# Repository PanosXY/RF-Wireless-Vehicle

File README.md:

RF-Wireless-Vehicle
===================

Wireless vehicle commanded through joystick, linked by RF signals

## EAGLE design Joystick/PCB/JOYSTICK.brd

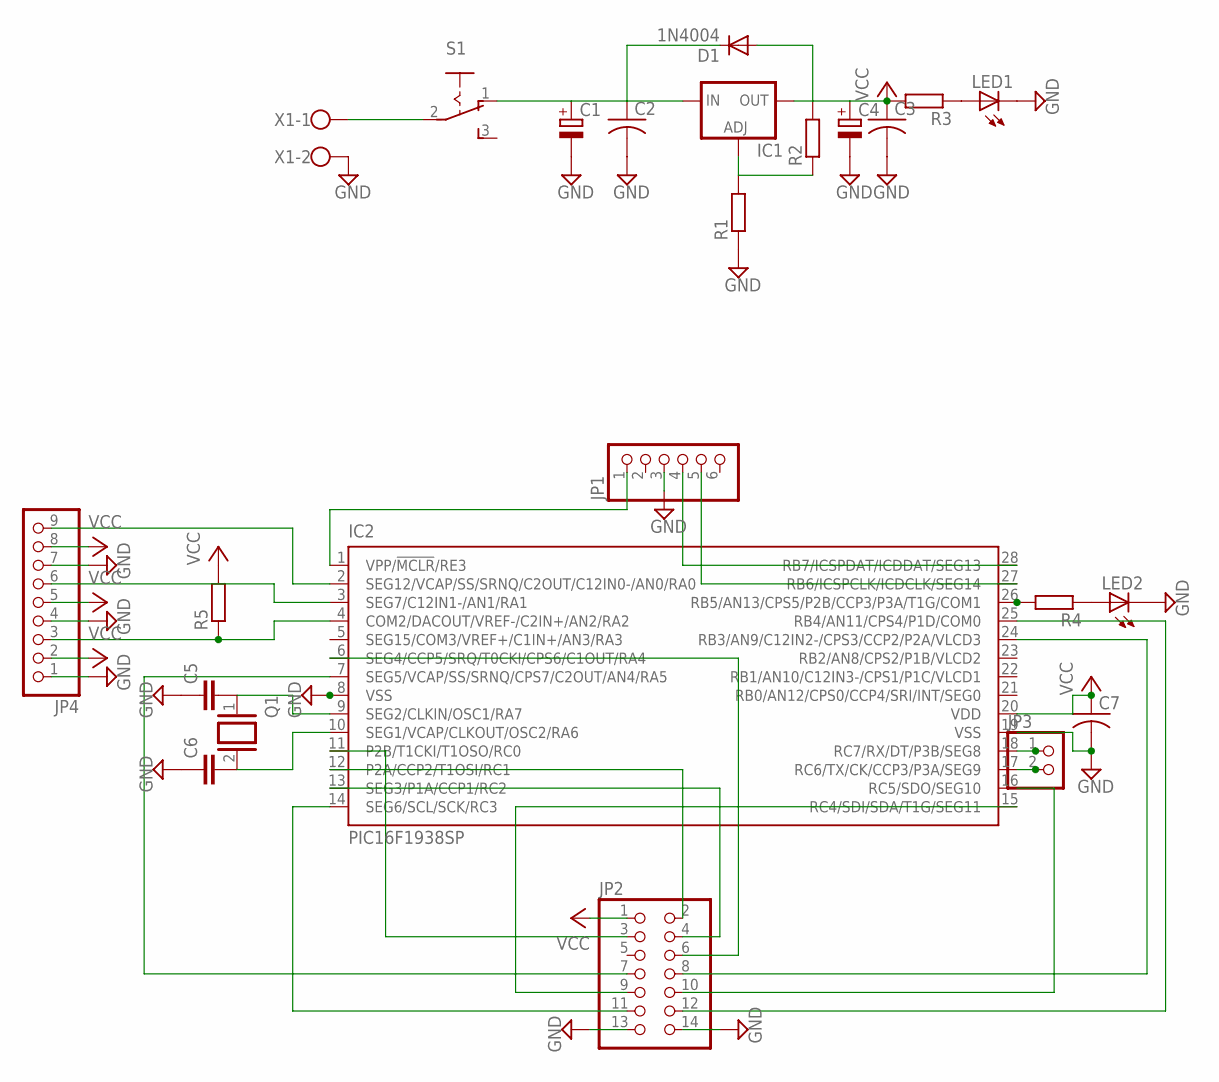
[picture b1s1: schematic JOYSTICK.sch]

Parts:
C1, C4: CPOL-EUE3.5-8; E3,5-8
C2, C3, C7: C-US050-030X075; C050-030X075
C5, C6: C-EU025-025X050; C025-025X050
D1: 1N4004; DO41-10
IC1: LM317TS; 317TS
IC2: PIC16F1938SP; DIL28-3
JP1: PINHD-1X6; 1X06
JP2: PINHD-2X7; 2X07
JP3: PINHD-1X2; 1X02
JP4: PINHD-1X9; 1X09
LED1, LED2: LED5MM
Q1: XTAL/S; QS
R1, R2, R3, R4, R5: R-EU_0207/10; 0207/10
S1: 255SB
X1: W237-102

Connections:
GND: C1.-, C2.2, C3.2, C4.-, C5.1, C6.1, C7.2, IC2.8 (VSS), IC2.19 (VSS), JP1.3, JP2.13, JP2.14, JP4.1, JP4.4, JP4.7, LED1.K (C), LED2.K (C), R1.1, X1.2
unnamed: S1.2, X1.1
unnamed: C1.+, C2.1, D1.C, IC1.3 (IN), S1.1 (O)
unnamed: IC2.11 (P2B/T1CKI/T1OSO/RC0), JP2.3
unnamed: LED1.A, R3.1
unnamed: IC1.1 (ADJ), R1.2, R2.1
unnamed: IC2.1 (VPP/!MCLR!/RE3), JP1.1
unnamed: IC2.2 (SEG12/VCAP/SS/SRNQ/C2OUT/C12IN0-/AN0/RA0), JP4.9
unnamed: IC2.3 (SEG7/C12IN1-/AN1/RA1), JP4.6
unnamed: IC2.4 (COM2/DACOUT/VREF-/C2IN+/AN2/RA2), JP4.3, R5.1
unnamed: IC2.12 (P2A/CCP2/T1OSI/RC1), JP2.2
unnamed: IC2.13 (SEG3/P1A/CCP1/RC2), JP2.4
unnamed: IC2.6 (SEG4/CCP5/SRQ/T0CKI/CPS6/C1OUT/RA4), JP2.6
unnamed: IC2.7 (SEG5/VCAP/SS/SRNQ/CPS7/C2OUT/AN4/RA5), JP2.7
unnamed: IC2.25 (RB4/AN11/CPS4/P1D/COM0), JP2.12
unnamed: IC2.24 (RB3/AN9/C12IN2-/CPS3/CCP2/P2A/VLCD3), JP2.8
unnamed: IC2.14 (SEG6/SCL/SCK/RC3), JP2.11
unnamed: IC2.15 (RC4/SDI/SDA/T1G/SEG11), JP2.9
unnamed: IC2.16 (RC5/SDO/SEG10), JP2.10
unnamed: IC2.17 (RC6/TX/CK/CCP3/P3A/SEG9), JP3.2
unnamed: IC2.18 (RC7/RX/DT/P3B/SEG8), JP3.1
unnamed: IC2.26 (RB5/AN13/CPS5/P2B/CCP3/P3A/T1G/COM1), R4.2
unnamed: IC2.27 (RB6/ICSPCLK/ICDCLK/SEG14), JP1.5
unnamed: IC2.28 (RB7/ICSPDAT/ICDDAT/SEG13), JP1.4
unnamed: C5.2, IC2.9 (SEG2/CLKIN/OSC1/RA7), Q1.1
unnamed: C6.2, IC2.10 (SEG1/VCAP/CLKOUT/OSC2/RA6), Q1.2
unnamed: LED2.A, R4.1
VCC: C3.1, C4.+, C7.1, D1.A, IC1.2 (OUT), IC2.20 (VDD), JP2.1, JP4.2, JP4.5, JP4.8, R2.2, R3.2, R5.2

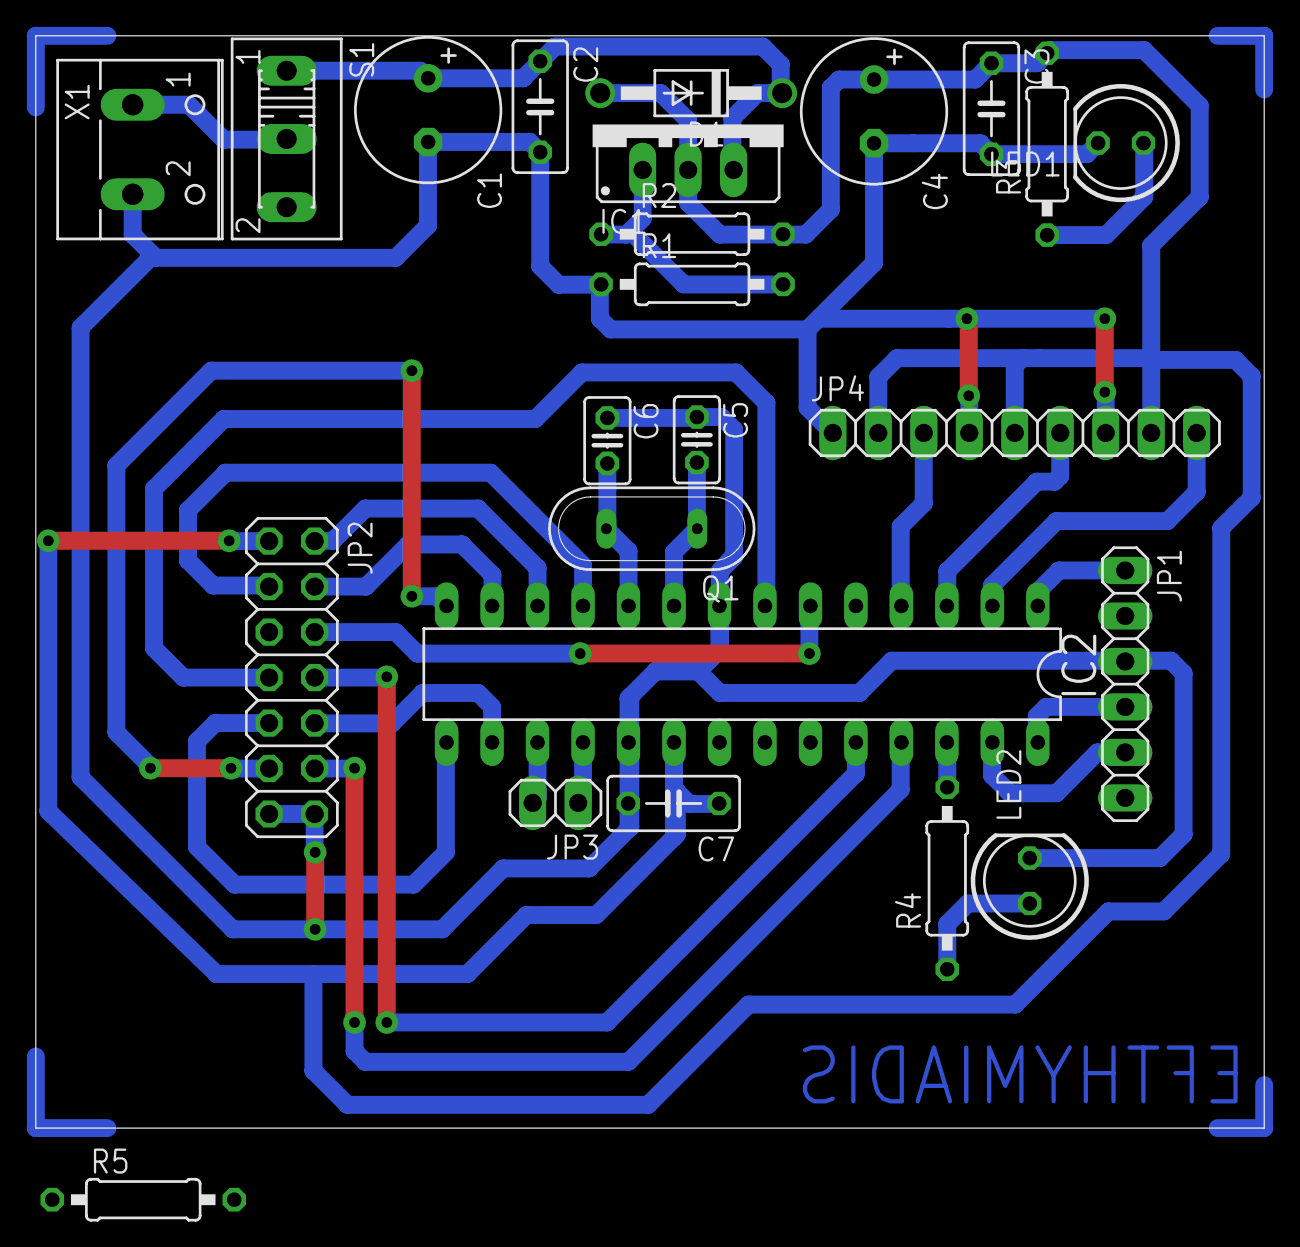
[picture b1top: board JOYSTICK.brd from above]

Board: 2 copper layers, 68.6 x 61.0 mm, 24 parts (0 on the bottom side), 28 nets.

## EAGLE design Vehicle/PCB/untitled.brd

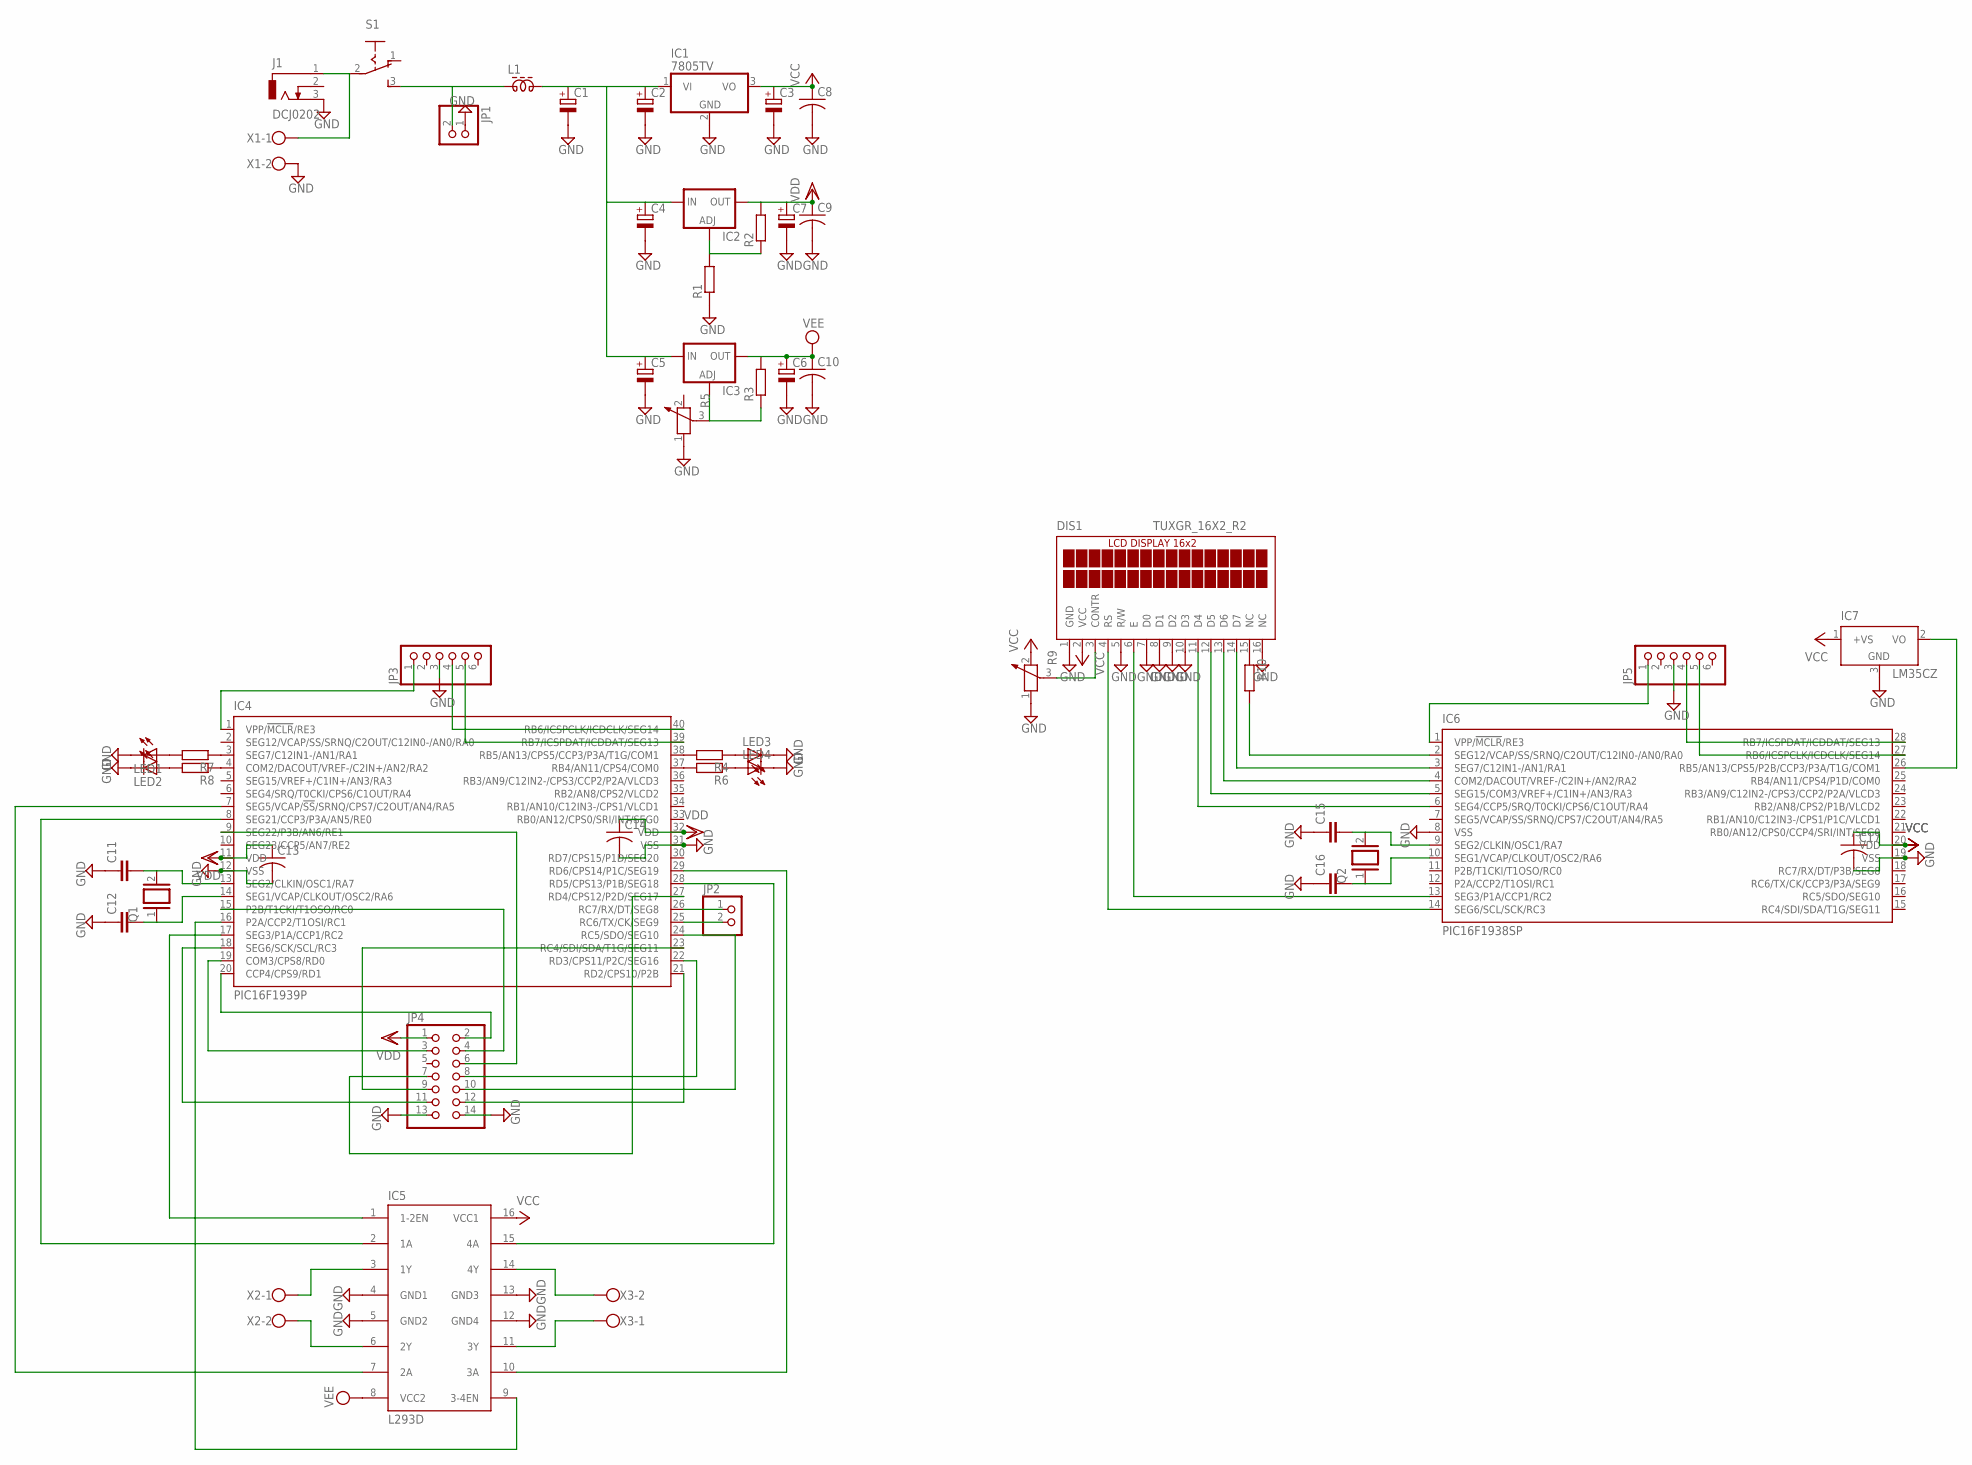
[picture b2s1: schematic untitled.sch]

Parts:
C1, C6: CPOL-EUE5-13; E5-13
C2, C3, C4, C5, C7: CPOL-EUE3.5-8; E3,5-8
C8, C9, C10, C13, C14, C17: C-US050-030X075; C050-030X075
C11, C12, C15, C16: C-EU025-025X050; C025-025X050
DIS1: TUXGR_16X2_R2
IC1: 7805TV; TO220V
IC2, IC3: LM317TS; 317TS
IC4: PIC16F1939P; DIL40
IC5: L293D; DIL16
IC6: PIC16F1938SP; DIL28-3
IC7: LM35CZ; TO92
J1: DCJ0202
JP1, JP2: PINHD-1X2; 1X02
JP3, JP5: PINHD-1X6; 1X06
JP4: PINHD-2X7; 2X07
L1: ZD60820512; ZD6-2W5
LED1, LED2, LED3, LED4: LED5MM
Q1, Q2: XTAL/S; QS
R1, R2, R3, R4, R6, R7, R8, R10: R-EU_0207/10; 0207/10
R5, R9: POTENTIOMETER_PT-10; PT-10
S1: 255SB
X1, X2, X3: W237-102

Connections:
GND: C1.-, C2.-, C3.-, C4.-, C5.-, C6.-, C7.-, C8.2, C9.2, C10.2, C11.1, C12.1, C13.2, C14.2, C15.1, C16.1, C17.2, DIS1.1 (GND), DIS1.5 (R/W), DIS1.7 (D0), DIS1.8 (D1), DIS1.9 (D2), DIS1.10 (D3), DIS1.16 (NC), IC1.2 (GND), IC4.12 (VSS), IC4.31 (VSS), IC5.4 (GND1), IC5.5 (GND2), IC5.12 (GND4), IC5.13 (GND3), IC6.8 (VSS), IC6.19 (VSS), IC7.3 (GND), J1.3, JP1.1, JP3.3, JP4.13, JP4.14, JP5.3, LED1.K (C), LED2.K (C), LED3.K (C), LED4.K (C), R1.1, R5.1, R9.1, X1.2
unnamed: JP1.2, L1.1, S1.3 (S)
unnamed: IC4.17 (SEG3/P1A/CCP1/RC2), IC5.1 (1-2EN)
unnamed: IC3.1 (ADJ), R3.1, R5.3
unnamed: J1.1, S1.2, X1.1
unnamed: C1.+, C2.+, C4.+, C5.+, IC1.1 (VI), IC2.3 (IN), IC3.3 (IN), L1.2
unnamed: IC4.26 (RC7/RX/DT/SEG8), JP2.1
unnamed: IC4.25 (RC6/TX/CK/SEG9), JP2.2
unnamed: IC2.1 (ADJ), R1.2, R2.1
unnamed: IC4.24 (RC5/SDO/SEG10), JP4.10
unnamed: IC4.1 (VPP/!MCLR!/RE3), JP3.1
unnamed: IC4.40 (RB6/ICSPCLK/ICDCLK/SEG14), JP3.4
unnamed: IC4.39 (RB7/ICSPDAT/ICDDAT/SEG13), JP3.5
unnamed: C12.2, IC4.14 (SEG1/VCAP/CLKOUT/OSC2/RA6), Q1.1
unnamed: C11.2, IC4.13 (SEG2/CLKIN/OSC1/RA7), Q1.2
unnamed: IC4.23 (RC4/SDI/SDA/T1G/SEG11), JP4.9
unnamed: IC4.18 (SEG6/SCK/SCL/RC3), JP4.11
unnamed: IC4.16 (P2A/CCP2/T1OSI/RC1), IC5.9 (3-4EN)
unnamed: IC4.20 (CCP4/CPS9/RD1), JP4.2
unnamed: IC4.19 (COM3/CPS8/RD0), JP4.3
unnamed: IC4.15 (P2B/T1CKI/T1OSO/RC0), JP4.4
unnamed: IC4.9 (SEG22/P3B/AN6/RE1), JP4.6
unnamed: IC4.27 (RD4/CPS12/P2D/SEG17), JP4.7
unnamed: IC4.21 (RD2/CPS10/P2B), JP4.12
unnamed: IC4.22 (RD3/CPS11/P2C/SEG16), JP4.8
unnamed: IC4.38 (RB5/AN13/CPS5/CCP3/P3A/T1G/COM1), R4.2
unnamed: IC4.37 (RB4/AN11/CPS4/COM0), R6.2
unnamed: IC4.3 (SEG7/C12IN1-/AN1/RA1), R7.1
unnamed: LED1.A, R7.2
unnamed: IC4.4 (COM2/DACOUT/VREF-/C2IN+/AN2/RA2), R8.1
unnamed: LED2.A, R8.2
unnamed: LED3.A, R4.1
unnamed: LED4.A, R6.1
unnamed: IC6.1 (VPP/!MCLR!/RE3), JP5.1
unnamed: IC4.28 (RD5/CPS13/P1B/SEG18), IC5.15 (4A)
unnamed: IC4.29 (RD6/CPS14/P1C/SEG19), IC5.10 (3A)
unnamed: IC4.8 (SEG21/CCP3/P3A/AN5/RE0), IC5.2 (1A)
unnamed: IC4.7 (SEG5/VCAP/!SS!/SRNQ/CPS7/C2OUT/AN4/RA5), IC5.7 (2A)
unnamed: IC5.3 (1Y), X2.1
unnamed: IC5.6 (2Y), X2.2
unnamed: IC5.14 (4Y), X3.2
unnamed: IC5.11 (3Y), X3.1
unnamed: IC6.28 (RB7/ICSPDAT/ICDDAT/SEG13), JP5.4
unnamed: IC6.27 (RB6/ICSPCLK/ICDCLK/SEG14), JP5.5
unnamed: C16.2, IC6.10 (SEG1/VCAP/CLKOUT/OSC2/RA6), Q2.1
unnamed: IC6.26 (RB5/AN13/CPS5/P2B/CCP3/P3A/T1G/COM1), IC7.2 (VO)
unnamed: IC6.2 (SEG12/VCAP/SS/SRNQ/C2OUT/C12IN0-/AN0/RA0), R10.2
unnamed: DIS1.3 (CONTR), R9.3
unnamed: DIS1.14 (D7), IC6.3 (SEG7/C12IN1-/AN1/RA1)
unnamed: DIS1.13 (D6), IC6.4 (COM2/DACOUT/VREF-/C2IN+/AN2/RA2)
unnamed: DIS1.12 (D5), IC6.5 (SEG15/COM3/VREF+/C1IN+/AN3/RA3)
unnamed: DIS1.11 (D4), IC6.6 (SEG4/CCP5/SRQ/T0CKI/CPS6/C1OUT/RA4)
unnamed: DIS1.6 (E), IC6.13 (SEG3/P1A/CCP1/RC2)
unnamed: DIS1.4 (RS), IC6.14 (SEG6/SCL/SCK/RC3)
unnamed: DIS1.15 (NC), R10.1
unnamed: C15.2, IC6.9 (SEG2/CLKIN/OSC1/RA7), Q2.2
VCC: C3.+, C8.1, C17.1, DIS1.2 (VCC), IC1.3 (VO), IC5.16 (VCC1), IC6.20 (VDD), IC7.1 (+VS), R9.2
VDD: C7.+, C9.1, C13.1, C14.1, IC2.2 (OUT), IC4.11 (VDD), IC4.32 (VDD), JP4.1, R2.2
VEE: C6.+, C10.1, IC3.2 (OUT), IC5.8 (VCC2), R3.2

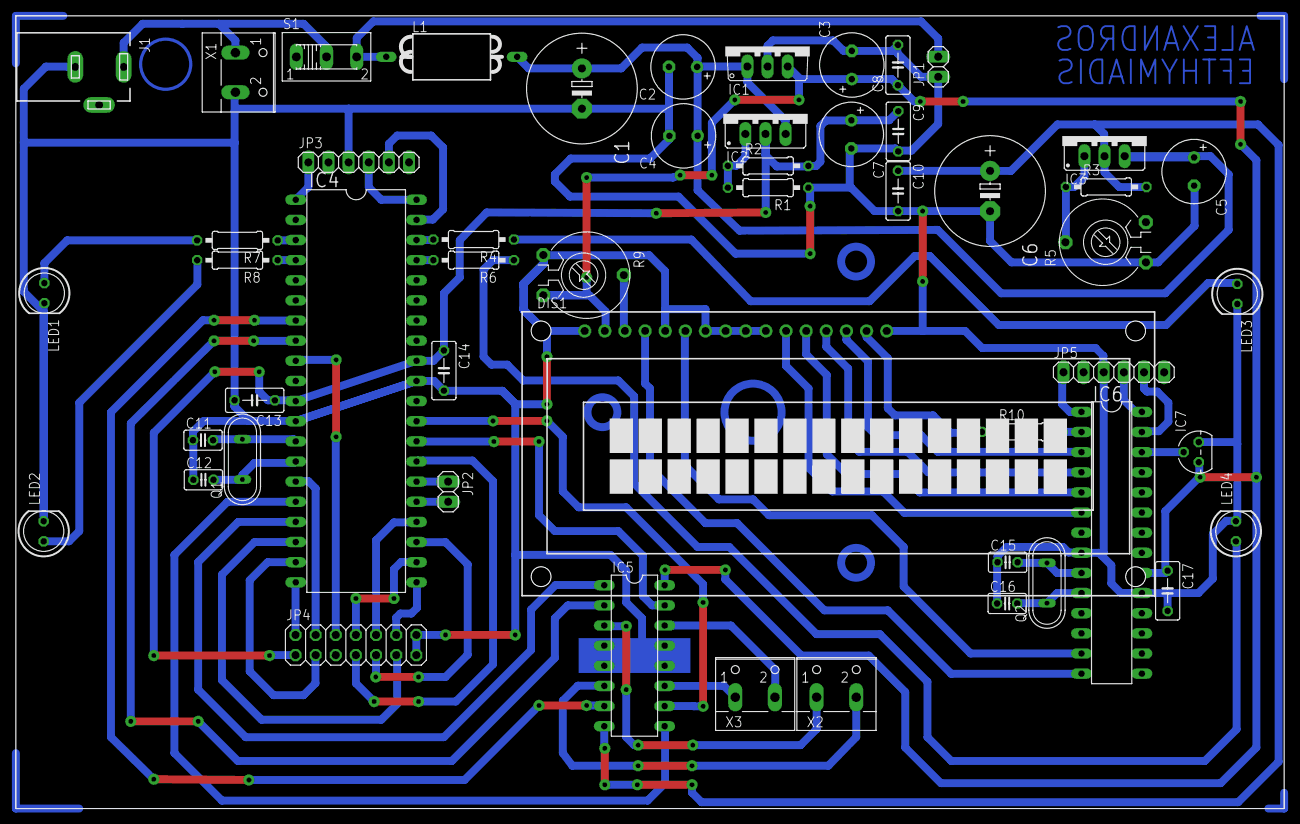
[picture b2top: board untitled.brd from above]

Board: 2 copper layers, 160.0 x 100.0 mm, 52 parts (0 on the bottom side), 59 nets.
